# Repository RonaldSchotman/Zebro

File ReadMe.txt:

This is the root of the Zebro Archive

Although the modules of different Zebro's should be interchangeable, they are organised according to the Zebro type that they are designed for.

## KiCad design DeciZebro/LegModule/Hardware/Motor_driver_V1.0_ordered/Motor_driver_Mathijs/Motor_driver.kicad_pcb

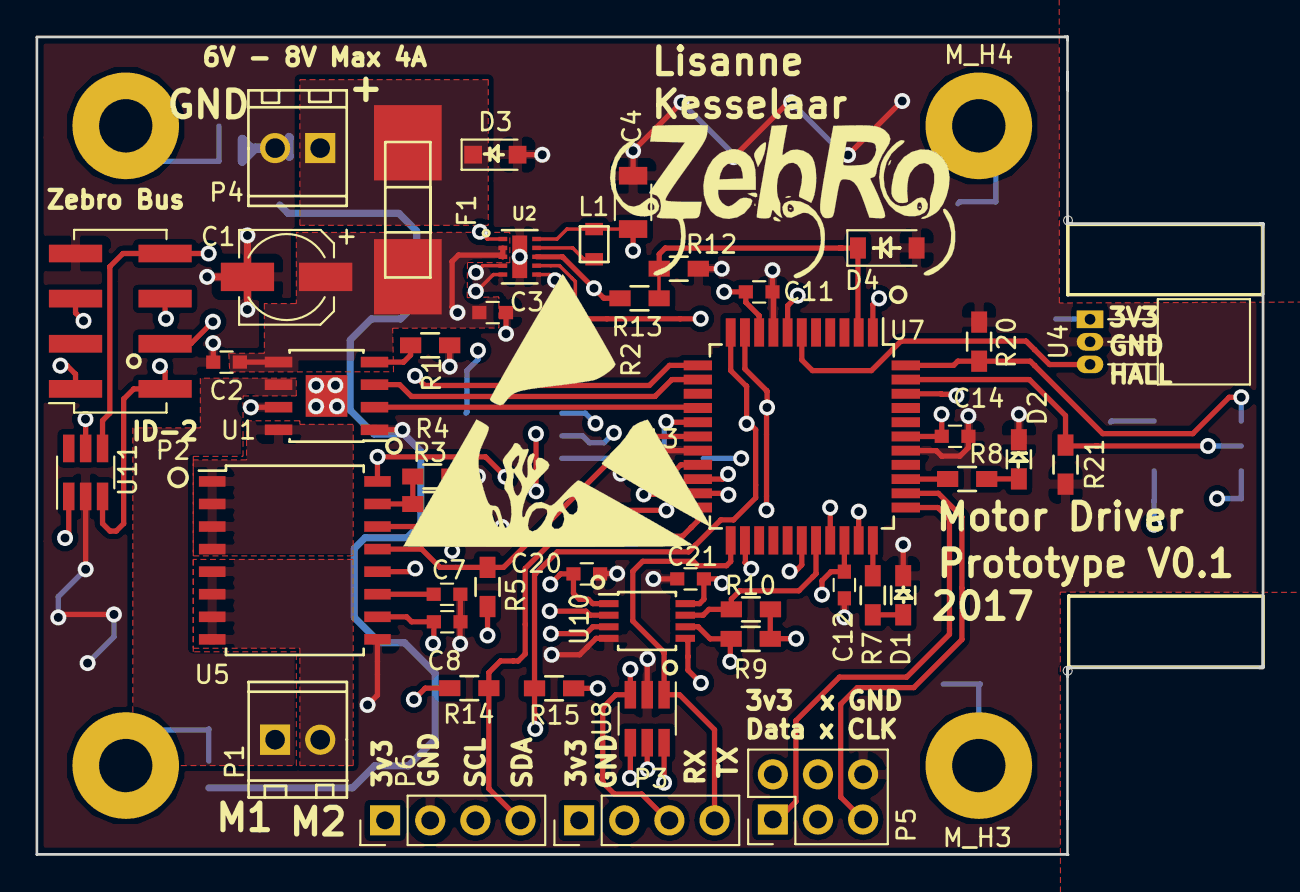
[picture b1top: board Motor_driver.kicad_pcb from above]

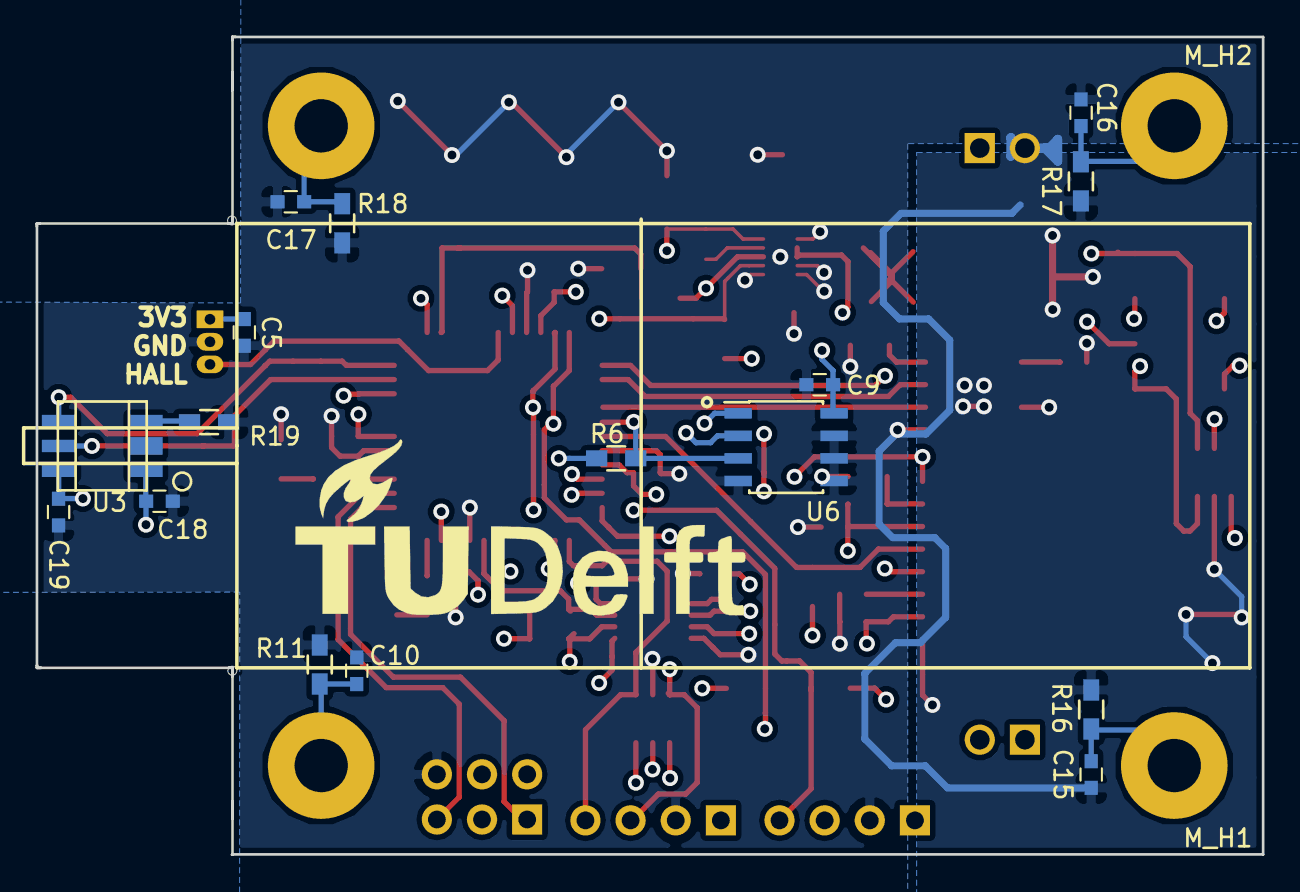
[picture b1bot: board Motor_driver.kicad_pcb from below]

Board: 4 copper layers, 69.0 x 46.0 mm, 68 parts (18 on the bottom side), 47 nets.

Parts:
C1: Bulk C; CP_Elec_5x5.3
C2, C10, C15, C16, C17: 1u; C_0603
C3: 2.2uF; C_0603
C4: 22uF; C_1206
C5, C6, C9, C11, C12, C13, C14, C18, C19, C20, C21: 100n; C_0603
C7, C8: 1n; C_0603
D1, D2: LED; R_0603_HandSoldering
D3: TVS_Uni; D_SOD-323_HandSoldering
D4: ZENER; D_SOD-123
F1: FUSE; litle_fuse_154_serie
L1: 10uH; Inductor-vishay-motor-driver
M_H1, M_H2, M_H3, M_H4: Mounting_Hole; MountingHole_3mm_Pad
P1, P4: CONN_02X01; screw_terimnal_2.54mm_pitch
P2: CONN_02X04; Socket_Strip_Straight_2x04_Pitch2.54mm_SMD
P3, P6: CONN_01X04; Pin_Header_Straight_1x04_Pitch2.54mm
P5: CONN_02X03; Pin_Header_Straight_2x03_Pitch2.54mm
R1: 16.9k; R_0603_HandSoldering
R2: 100k; R_0603_HandSoldering
R3: 10k; R_0603_HandSoldering
R4: 22k; R_0603_HandSoldering
R5: 330k; R_0603_HandSoldering
R6, R9, R10, R14, R15: 2k7; R_0603_HandSoldering
R7, R8: 120; R_0603_HandSoldering
R11, R16, R17, R18: 1M; R_0603_HandSoldering
R12: 47k; R_0603_HandSoldering
R13: 68k; R_0603_HandSoldering
R19, R20, R21: 150E; R_0603_HandSoldering
U1: DRV8871; SOIC-8-1EP_3.9x4.9mm_Pitch1.27mm
U2: TPS62177; WSON-10-2x3
U3: TCUT1350
U4: SM451; TO-92_Horizontal2_Inline_Narrow_Oval
U5: ACS710; SOIC-16W_7.5x10.3mm_Pitch1.27mm
U6: NCT75; SOIC-8_3.9x4.9mm_Pitch1.27mm
U7: ATXMEGA32D4-A; LQFP-44_10x10mm_Pitch0.8mm
U8, U11: TVS_4_I/O; SOT-23-6_Handsoldering
U10: PCA9517; TSSOP-8_3x3mm_Pitch0.65mm

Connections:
+3.3VP: C20.1, P2.4, U10.1
+3V3: C4.1, C5.1, C6.1, C9.1, C11.2, C12.2, C13.2, C14.2, C18.1, C19.1, C21.1, L1.2, P3.1, P5.2, P6.1, R2.1, R3.1, R5.1, R6.1, R9.1, R10.1, R14.1, R15.1, U2.10, U3.1, U3.6, U4.1, U5.14, U6.8, U7.9, U7.19, U7.31, U7.39, U8.5, U10.8, U11.5
/Buck_converter/PG: R2.2, U2.7, U7.7
/Connectors/EN_I2C: U7.32, U10.5
/Connectors/ID-1: P2.1, U7.20, U11.1
/Connectors/ID-2: P2.2, U7.21, U11.3
/Connectors/INT: P2.8, U7.12, U11.4
/Connectors/M1: P1.2, U1.6
/Connectors/M2: P1.1, U5.5, U5.6, U5.7, U5.8
/Connectors/PDI_CLK: P5.5, U7.35, U8.4
/Connectors/PDI_DATA: P5.1, U7.34, U8.6
/Connectors/RX: P3.3, U7.22, U8.3
/Connectors/SCLA: P2.6, U10.2
/Connectors/SCL_M: R10.2, U7.29, U10.7
/Connectors/SDAA: P2.5, U10.3
/Connectors/SDA_M: R9.2, U7.28, U10.6
/Connectors/TX: P3.4, U7.23, U8.1
/Connectors/V_P: D3.1, F1.1, P4.2
/Driver/M2_S: U1.8, U5.1, U5.2, U5.3, U5.4
/Driver/PWM1: U1.3, U7.13
/Driver/PWM2: U1.2, U7.15
/SCL_SL: P6.3, R15.2, U6.2, U7.11
/SDA_SL: P6.4, R14.2, U6.1, U7.10
/Sensor/ENCODER_1: R21.1, U3.5, U7.43
/Sensor/ENCODER_2: R20.1, U3.4, U7.44
/Sensor/HALL: U4.3, U7.6
/Sensor/V_Imotor: U5.12, U7.1
/Sensor/V_Imotor0V: C8.1, U5.10, U7.42
/Sensor/current_sense_fault_en: U5.16, U7.24
/Sensor/~ALERT_TEMP: R6.2, U6.3, U7.16
/Sensor/~FAULT_CURRENT: R5.2, U5.13, U7.17
/Xmega/LED: R8.1, U7.36
GND: C1.2, C2.2, C3.2, C4.2, C5.2, C6.2, C7.2, C8.2, C9.2, C10.2, C11.1, C12.1, C13.1, C14.1, C15.2, C16.2, C17.2, C18.2, C19.2, C20.2, C21.2, D1.1, D2.1, D3.2, D4.2, P2.7, P3.2, P4.1, P5.6, P6.2, R1.1, R4.2, R11.2, R12.2, R16.2, R17.2, R18.2, R19.2, R20.2, R21.2, U1.1, U1.7, U1.9, U2.1, U2.4, U2.5, U2.6, U2.EP, U4.2, U5.9, U6.4, U6.5, U6.6, U6.7, U7.8, U7.18, U7.30, U7.38, U8.2, U10.4, U11.2
unnamed: C7.1, U5.11
unnamed: C10.1, M_H3.1, R11.1
unnamed: C15.1, M_H1.1, R16.1
unnamed: C16.1, M_H2.1, R17.1
unnamed: C17.1, M_H4.1, R18.1
unnamed: D1.2, R7.2
unnamed: D2.2, R8.2
unnamed: D4.1, R12.1, R13.2, U7.2
unnamed: L1.1, U2.9
unnamed: R1.2, U1.4
unnamed: R3.2, R4.1, U5.15
unnamed: R7.1, U7.33
unnamed: R19.1, U3.3
VPP: C1.1, C2.1, C3.1, F1.2, R13.1, U1.5, U2.2, U2.3, U2.8

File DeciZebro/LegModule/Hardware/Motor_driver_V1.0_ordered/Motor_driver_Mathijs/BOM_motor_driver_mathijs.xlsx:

BOM power system
 |  |  |  |  | Total price | 33.364100000000001
Description | Value | Schematic Sheet | KiCad reference | Amount | Price | Price total | Manufacuter | Supplier | Ordercode | Artikel nr. | link
Resistors
Resistor 0603 | 120E |  | R7, R8 | 2 | 1.26E-2 | 1.26E-2 | YAGEO | Farnell | 9238379 | RC0603FR-07120RL | Link
Resistor 0603 | 150E |  | R19, R20, R21 | 3 | 1.03E-2 | 3.09E-2 | WELWYN | Farnell | 2078902 | ASC0603-150RFT5 | Link
Resistor 0603 | 2k7 | ATXmega, Driver, Sensors | R6, R9, R10, R14, R15 | 5 | 0.01 | 0.05 | WALSIN | Farnell | 2502439 | WR06X2701FTL | Link
Resistor 0603 | 10k | Driver, ATXmega | R3 | 1 | 3.8E-3 | 3.8E-3 | Multicomp | Farnell | 2447230 | MCWR06X1002FTL | Link
Resistor 0603 | 16.9k |  | R1 | 1 | 3.5000000000000001E-3 | 3.5000000000000001E-3 | Multicomp | Farnell | 2447263 | MCWR06X1692FTL | Link
Resistor 0603 | 22k |  | R4 | 1 | 3.2000000000000002E-3 | 3.2000000000000002E-3 | Multicomp | Farnell | 2447299 | MCWR06X2202FTL | Link
Resistor 0603 | 47k |  | R12 | 1 | 3.2000000000000002E-3 | 3.5000000000000001E-3 | Multicomp | Farnell | 2447376 | MCWR06X4702FTL | Link
Resistor 0603 | 68k |  | R13 | 1 | 3.5000000000000001E-3 | 3.5000000000000001E-3 | Multicomp | Farnell | 2447420 | MCWR06X6802FTL | Link
Resistor 0603 | 330k |  | R5 | 1 | 4.0000000000000001E-3 | 4.0000000000000001E-3 | Multicomp | Farnell | 2447338 | MCWR06X3303FTL | Link
Resistor 0603 | 100k | Buck Converter | R2 | 1 | 7.9000000000000008E-3 | 7.9000000000000008E-3 | YAGEO | Farnell | 9238727 | RC0603FR-07100KL | Link
Resistor 0603 | 1M |  | R11, R16, R17, R18 | 4 | 1.2999999999999999E-3 | 5.1999999999999998E-3 | Multicomp | Farnell | 9330410 | MC0063W060311M | Link
Capacitors
Capacitor 0603 | 1u | Driver | C2, C10, C15, C16, C17 | 2 | 2.5100000000000001E-2 | 5.0200000000000002E-2 | Murata | Farnell | 9527699 | GRM188R60J105KA01D | Link
Capacitor 0603 | 100nF | Sensors, ATXmega | C5, C6, C9, C11, C12, C13, C14, C18, C19, C20, C21 | 11 | 1.29E-2 | 0.1419 | WALSIN | Farnell | 2496833 | 0603B104K250CT | Link
Capacitor 0603 | 2.2u | Buck Converter | C3 | 1 | 9.8599999999999993E-2 | 9.8599999999999993E-2 | Murata | Farnell | 2611926 | GRM188R6YA225KA12D | Link
Capacitor 1206 | 22u | Buck Converter | C4 | 1 | 0.28100000000000003 | 0.28100000000000003 | YAGEO | Farnell | 1458914 | CC1206KKX5R5BB226 | Link
Capacitor 0603 | 1n |  | C7, C8 | 2 | 5.8999999999999999E-3 | 1.18E-2 | Multicomp | Farnell | 2627426 | MC0603B102K250CT | Link
Capacitor | 22u |  | C1 | 1 | 1.4E-2 | 1.4E-2 | Multicomp | Farnell | 2611332 | MCVKZ016M220DA1L | Link
Diodes
LED | KPH-1608SGC | ATXmega | D1, D2 | 2 | 4.4400000000000002E-2 | 8.8800000000000004E-2 | Kingbright | Farnell | 2426215 | KPH-1608SGC | Link
TVS | CDSOD323-T08 | Connectors | D3 | 1 | 2.3599999999999999E-2 | 2.3599999999999999E-2 | Bourns | Farnell | 2341919 | CDSOD323-T08 | Link
Zener | MMSZ4684 |  | D4 | 1 | 6.1100000000000002E-2 | 6.1100000000000002E-2 | Fairchild | Farnell | 2454044 | MMSZ4684 | Link
Inductors
Inductor | 10uH | Buck Converter | L1 | 1 | 0.59399999999999997 | 0.59399999999999997 | Vishay/Dale | Mouser | 70-IFSC1515AHER100M0 | IFSC1515AHER100M01 | Link
IC's
DRV8871 | Motor driver | Motor system | U1 | 1 | 2.7 | 2.7 | TI | Mouser | 595-DRV8871DDAR | DRV8871DDAR | Link
SM451 | Hall-sensor | Sensors | U4 | 1 | 0.97099999999999997 | 0.97099999999999997 | Honeywell | Mouser | 785-SM451R | SM451R | Link
NCT75MNR2G | Temperature sensor | Sensors | U6 | 1 | 0.60399999999999998 | 0.60399999999999998 | On Semiconductor | Mouser | 863-NCT75DR2G | NCT75DR2G | Link
TPS62177 | Buck Converter | Buck Converter | U2 | 1 | 1.44 | 1.44 | TI | Mouser | 595-TPS62177DQCR | TPS62177DQCR | Link
ATXMEGA32D4 | ATXMEGA | Xmega | U7 | 1 | 2.87 | 2.87 | Atmel | Farnell | 1748558 | ATXMEGA32D4-AU | Link
TCUT1350 | Photo Encoder | Sensors | U3 | 2 | 1.57 | 3.14 | Vishay | Farnell | 2424451 | TCUT1350X01 | Link
ACS710 | Current Sensor | Sensors | U5 | 1 | 4.17 | 4.17 | Allegro | Farnell | 2057422 | ACS710KLATR-6BB-T | Link
SRV05 | TVS diode 4 I/O |  | U18, U11 | 2 | 1.53 | 3.06 | Bourns | Farnell | 1824870 | CDSOT23-SRV05-4 | Link
PCA9517 | Buffer | Connectors | U10 | 1 | 0.91200000000000003 | 0.91200000000000003 | NXP | Farnell | 2212064 | PCA9517ADP | Link
Overig
Conn 01x04 |  | Connectors | P3, P6 | 1 | 0.16300000000000001 | 0.16300000000000001 | Wurt Elektronik | Farnell | 2356155 | 61300411121 | Link
Conn 02x01 screw |  | Connectors | P1, P4 | 2 | 0.93700000000000006 | 1.8740000000000001 | TE | Farnell | 2112482 | 282834-2 | Link
Conn 02x03 |  | Connectors | P5 | 1 | 0.161 | 0.161 | Harwin | Farnell | 1022231 | M20-9980346 | Link
Conn 02x04 smd | Data | Connectors | P2 | 1 | 0.54600000000000004 | 0.54600000000000004 | Samtec | Farnell | 2056012 | TSM-104-02-T-DV | Link
Fuse |  |  |  | 1 | 2.72 | 2.72 | Littlefuse | Farnell | 9922407 | 0452004.NRL | Link
Fuse holder |  | Connectors | F1 | 1 | 6.54 | 6.54 | Littlefuse | Farnell | 9943765 | 0154004.DRT | Link

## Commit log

2017-02-13 Start of Team list
2017-02-13 Added sandbox Added gitignore to sandbox
2017-02-14 Changed gitignore
2017-02-15 added my name!
2017-02-20 Added Standard References: Codeguide, Styleguide, and Zebrobus standard specification
2017-02-21 test
2017-02-24 Added Deci Zebro Leg Module hardware KiCad design files and documentation
2017-02-27 Pico Zebro Demo Starting code files
2017-02-27 message test? getting errors (readme has some text now)
2017-02-28 Maybe a py script for determing Pico Zebro orientation in Demo
2017-03-02 Added Atmel-studios project and reference documents of the mcu, got toolchain working, verfied with shining led
2017-03-02 blinking led!!!!1!, added .pdf to gitignore
2017-03-03 Added global interrupt control
2017-03-03 implemented vregs
2017-03-03 started to implement UART on the leg module, not finished yet
2017-03-06 Changes to PicoZevro Demo about orientation determination
2017-03-07 added my name
2017-03-07 added working code for stand up KiloZebro
2017-03-07 Added my name :O
2017-03-07 added new zebrobus protocol for more precise timing
2017-03-07 added personal details to team info
2017-03-08 Update on code Major update, starting now regular commiting and at the end of the day push
2017-03-08 changes to determing orientation in step 3 oforient.py program
2017-03-08 working step 3 for determing angle in calculations not with pixels yet
2017-03-08 working step 3 WE CAN SEE WHITE
2017-03-08 live feed orientation detection works for step 3 well step 1 and 2 need improvement
2017-03-08 live feed orientation detection works for step 3 well step 1 and 2 need improvement, working on step 2 now
2017-03-08 resolution needed to change for FOV
2017-03-08 resolution needed to change for FOV Not working part 2 :(
2017-03-09 Continiueing on UART, implemented DMA feed
2017-03-09 improved hysteresis, encoder wrap around and position control. Also added crude current-limiter.
2017-03-10 optimized walking positions, implemented real over-current protection, added panic stop, set position check to == instead of range. Proved to walk.
2017-03-10 added folder with original KiCad files.
2017-03-13 Starting in new file PZDemo_OpenCV for better results and calibration techniques
2017-03-13 Calibration pi camera pictures
2017-03-13 Calibration in PZ_Demo_Opencv after Calibration testing setup 1 (not working yet)
2017-03-13 Calibration in PZ_Demo_Opencv after Calibration testing setup 1 (maybe working yet)
2017-03-13 In PZDemo_OpenCV able to detect green pretty well and able to say how many Zebros are found in a array
2017-03-13 In PZDemo_OpenCV able to detect green and starting again with getting QR Code. It is not working yet
2017-03-14 UART finished, but now i have 10^6 problems because of a device change
2017-03-14 Update on recognizing stuff in PZ Demo and starting with learning bluetooth connection which can only be tested when there is an actual PZ
2017-03-14 extra picture for shwoing what could be done
2017-03-14 implemented PID control in motion_move_to_point
2017-03-15 Cleaning up the map and improving README.
2017-03-16 Working Threads with looking for bluetooth devices works in Thread.py One threads finds them the other can use the founded data
2017-03-16 lots of testing files and Threads with bluetooth (search) working in Threads.py
2017-03-16 detection.py went back to working
2017-03-17 Tesing done for detecting Pico Zebro
2017-03-17 Lots of testing data on detection mostly
2017-03-17 renaming pictures
2017-03-17 Denoise Test (dont do this uses 100% cpu) also clean up map
2017-03-17 First training python script
2017-03-17 Uart still not working
2017-03-20 OpenCV haar classifier Testing (lots of pics)
2017-03-20 OpenCV classifiers testing (nothing working yet)
2017-03-21 Walking code for the pico zebro
2017-03-21 Lots of changes/testing classifiers and current project is Fallback
2017-03-21 changed pwm to centre-aligned and made sure ADC still works. Duty_cycle is not between 0-1023
2017-03-22 Adjustments to detecting and controlling with Fallback Scenario
2017-03-22 As far as possible without working Fallback_ZebroDEmo code (pseudo code mostly)
2017-03-23 A lot of testing in Fallback GPIO to make detection faster without succes
2017-03-23 Now working code in Fast_detection.py (still needs improvement
2017-03-23 Added hbridge, fixed some UART errors
2017-03-24 cpp with raspbicam not doable and Uart test in python need to enable uart in boot config file
2017-03-24 H-bridge working, adder error handling, started implementing i2c
2017-03-24 Movement trying to get pseud code in Fast_detect and testing coordinates
2017-03-27 In Fast Detection V2 the pseudo code in real code only (maybe???) works for 2 PZ
2017-03-28 implemented rudimentary current control
2017-03-29 changes and testing of Fast_detection_V2
2017-03-29 important changes to Fast_Detection_V2 for blocking
2017-03-29 if correct now all y and x are on the right place with Fast_Detection_V2
2017-03-29 In Fast_detection_V2 is now working (In as no syntax errors) but need to find out communication
2017-03-29 Fast_Detection error solutions
2017-03-29 implemented working PI-control for current. Ki= 30, Kp = 30
2017-03-30 Finished current-pi controller. p=28 and i=20.
2017-03-31 except for the lock on uart write in theorie working Fast_Detection_V2
2017-03-31 QUEUE_MAIN_Test.py as proof Fast_Detection has to work when the lock if the serial works
2017-03-31 made one correction with reseting the code (it didnt before when needed)
2017-03-31 added position PID. Need to tune I and D. D needs more time because encoder is not so good, but we're getting there. Needs a little more weight.
2017-04-03 Version uploaded with header files, no implemented decision function
2017-04-03 Version with dummy decision function, makefile added.
2017-04-03 Locomotion with updated readme.txt
2017-04-03 Until actual testing with Pico Zebro's can be done Fast_Detection_V3 should work
2017-04-03 implemented position pid control with p=150, i=180, d=30.
2017-04-04 raspberry.py for control Pico Zebro from Haagse school
2017-04-04 implemented zebrobus and basic motion controller
2017-04-04 I Think a complete working version for 1 Zebro in Queue Main Test V3 with comments
2017-04-04 I Think a complete working version for 1 Zebro in Queue Main Test V3 with comments For real now had the connections within control still wrong
2017-04-04 In Pico_Demo_V1 Should be a version that may work for 10 Pico Zebros
2017-04-04 Fixed i2c enable bug, added basic motion control, added arduino sketch for accessing zebrobus which does not work yet
2017-04-05 Better working tracking system wih less bluetooth errors
2017-04-05 More comments with how the code works and a possible solution for keeping detming the direction where every Zebro is going needs to be tested
2017-04-05 more comments
2017-04-07 Some improvements in comments in Queue_Main_test_V3 and maybe and even better merhod in Queue_Main_test_V4 which should work with only light where movement matters not but only the light (it works fo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
2017-04-07 Just some things
2017-04-10 Made some improvements in code Queue_Mian_Test_V3 mostly with direction needs to be better tho
2017-04-11 more improvements only problem is some frames zebro is lost
2017-04-11 Measurements and a new code for new algoritm for tracking needs more testing
2017-04-12 A seemingly working code for 1 Pico Zebro in Queue_Main_Test_V5 needs more testing with a proper Pico Zebro which can actually walk
2017-04-12 work in progress in QUEue_Main_Test_V6 for 8 Pico Zebros with Queue_Main_Test_V5 still has to work only needs proper test with Pico Zebro
2017-04-13 Queue_Main_Test_V6 should be ready for 8 PicoZebro control now needs testing to confirm
2017-04-13 Do not toucj Queue_Main_Test_V7 it is working for 1 Pico Zebro
2017-04-13 Working in V8 for multiple Zebro's
2017-04-18 making versions for multiple Pico Zebro in Zebro Demo V1 with amount of pico's behind that
2017-04-18 Need more testing
2017-04-18 Added setpoint generator. Left and right leg unfortunately have different code.
2017-04-18 use Zebro_demo V3 2
2017-04-19 Locomotion main file cleaned up, now working for the Mastodont with place and time sending
2017-04-19 working walking, non-working calibration
2017-04-21 working calibration and added emergency stop handling inside zebro_control function.
2017-04-25 averaging address detection, constant speed setpoint-generator, updated pootbus
2017-04-26 updated PID position control, Emergency still needs work, calibration still not 100%, very simple setpoint generator
2017-04-28 fully functional calibration, emergency state is now safe.
2017-05-02 implemented walking backward and battery voltage monitoring
